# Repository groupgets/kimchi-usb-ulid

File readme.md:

# kimχ micro lid KiCad project template

This template lets you create lid expansion boards for the [kimχ micro i.MX8M Mini SBC](https://labs.groupgets.com/kimchi-micro).

This project should include everything you need to make an expansion board, including an eeprom
that can be used to identify your lid and automatically load the correct configuration files (with
some software work to support this).

## How to use this project

This project is to be used with KiCad's "New Project from Template" function.

### Download with GitHub

On GitHub you can select Clone or Download -> Download Zip, and save into your KiCad templates directory. The user template directory is $HOME/kicad/template/

In KiCad, select File > New Project > New Project From Template, and select User Templates. You can then select the kimχ micro - LID project in this list.

### Clone with GitHub

Alternatively, you can create a new GitHub project from this template by selecting Use This Template, above. From there you clone the new project locally and open it directly with KiCad.

Important Note
============
GroupGets does not provide coding, firmware, or software support of any kind and will not respond to related requests. All software and firmware provided by GroupGets are offered solely as examples or potential starting points. These repositories may be outdated and are not guaranteed to function as intended.

We do not accept returns or offer replacements due to issues related to software, firmware, or code compatibility.

The software is provided "AS IS", without warranty of any kind, express or implied, including but not limited to the warranties of merchantability, fitness for a particular purpose and non-infringement. In no event shall the authors or copyright holders be liable for any claim, damages, or other liability, whether in an action of contract, tort, or otherwise, arising from, out of, or in connection with the software or the use or other dealings in the software.

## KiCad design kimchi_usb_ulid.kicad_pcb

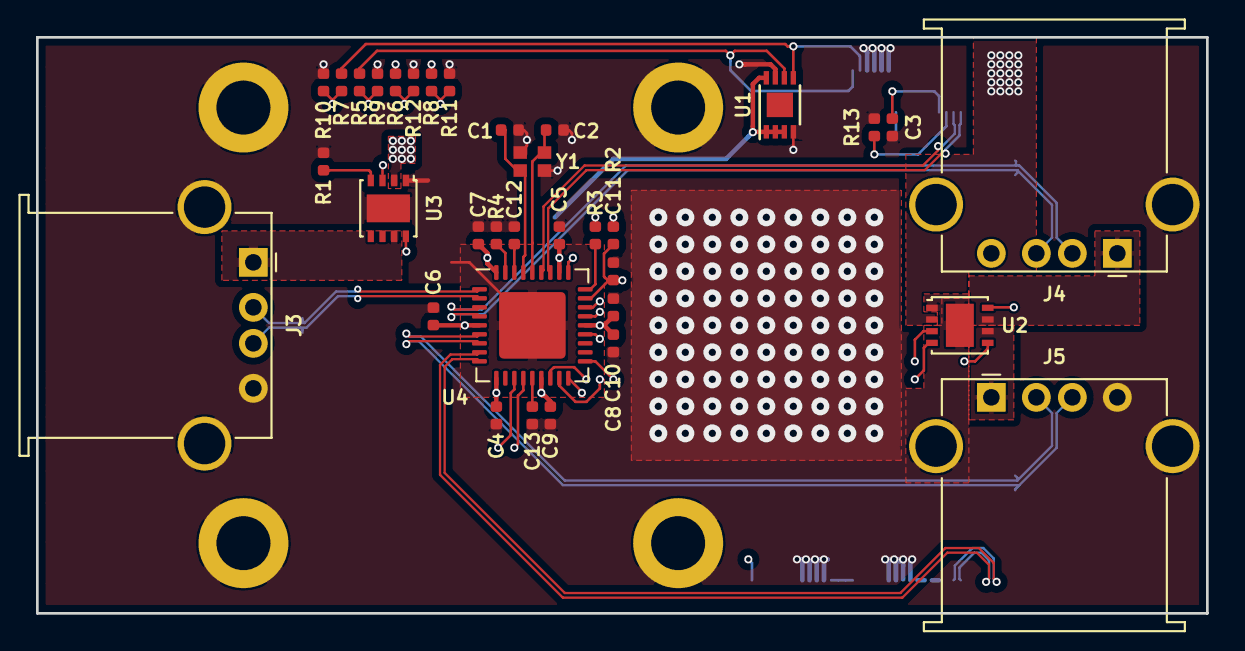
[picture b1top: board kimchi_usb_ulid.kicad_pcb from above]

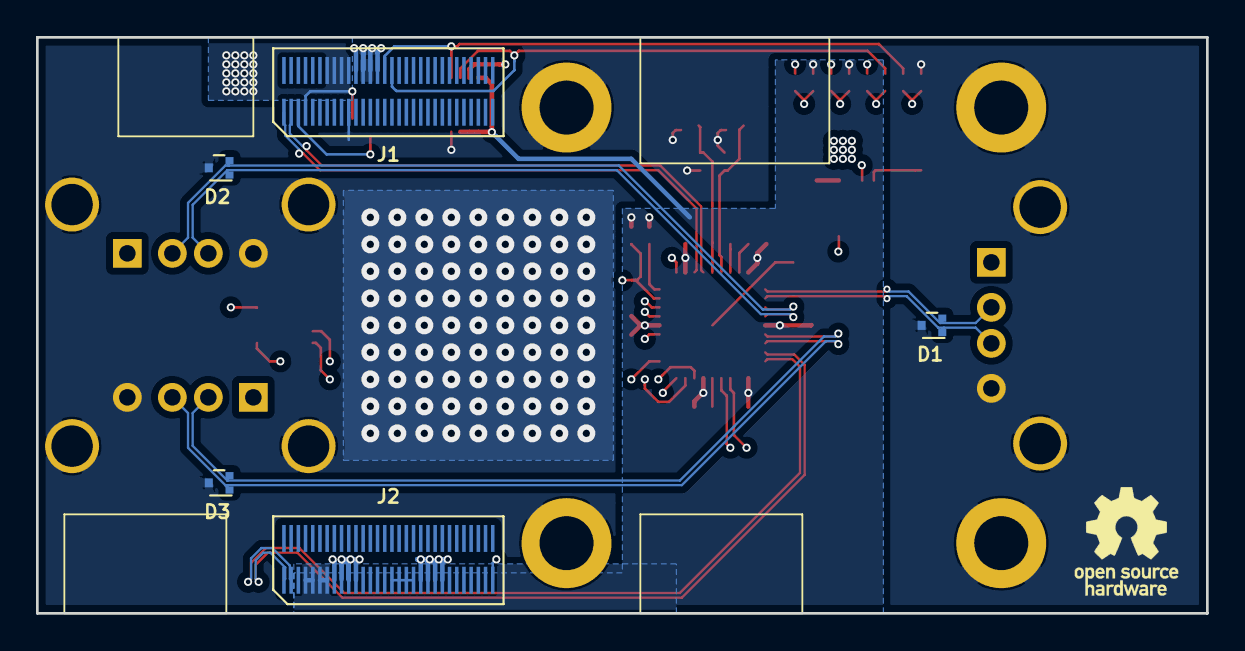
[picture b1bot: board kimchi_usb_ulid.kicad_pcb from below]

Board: 4 copper layers, 65.0 x 32.0 mm, 44 parts (6 on the bottom side), 38 nets.

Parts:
C1, C2: 18pF 1%; C_0402_1005Metric
C3: 1uF; C_0402_1005Metric
C4, C5, C6, C7, C8, C9, C11, C12, C13: 0.1uF; C_0402_1005Metric
C10: 4.7uF; C_0402_1005Metric
D1, D2, D3: D_TVS_x2_AAC; SOT-723
H1, H2, H3, H4: MountingHole_Pad; MountingHole_3mm_Pad
J1, J2: DF40HC(3.5)-60DS
J3, J4, J5: USB_A; USB_A_Stewart_SS-52100-001_Horizontal
LOGO1: Logo_Open_Hardware_Small; OSHW-Logo_5.7x6mm_SilkScreen
R1: 10K; R_0402_1005Metric
R2, R3, R6, R8, R9, R10, R11, R12, R13: 100K; R_0402_1005Metric
R4: 12K 1%; R_0402_1005Metric
R5, R7: 0; R_0402_1005Metric
U1: 24C32; DFN-8-1EP_3x2mm_P0.5mm_EP1.36x1.46mm
U2, U3: AP2152A; DFN-8-1EP_3x3mm_P0.65mm_EP1.55x2.4mm
U4: USB2514B_Bi; QFN-36-1EP_6x6mm_P0.5mm_EP3.7x3.7mm
Y1: 24MHz 50 PPM; XRCGB

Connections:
/USB_DN1_DN: D1.2, J3.2, U4.1
/USB_DN1_DP: D1.1, J3.3, U4.2
/USB_DN1_EN: U3.3, U4.12
/USB_DN1_FLG: U3.8, U4.13
/USB_DN1_VBUS: J3.1, U3.7
/USB_DN2_DN: D2.2, J4.2, U4.3
/USB_DN2_DP: D2.1, J4.3, U4.4
/USB_DN2_EN: U2.3, U4.16
/USB_DN2_FLG: U2.8, U4.17
/USB_DN2_VBUS: J4.1, U2.7
/USB_DN3_DN: D3.2, J5.2, U4.6
/USB_DN3_DP: D3.1, J5.3, U4.7
/USB_DN3_EN: U2.4, U4.18
/USB_DN3_FLG: U2.5, U4.19
/USB_DN3_VBUS: J5.1, U2.6
GND: C1.1, C2.1, C3.2, C4.1, C5.1, C6.1, C7.1, C8.1, C9.1, C10.1, C11.1, C12.1, C13.1, D1.3, D2.3, D3.3, H1.1, H2.1, H3.1, H4.1, J1.11, J1.12, J1.13, J1.14, J1.51, J2.38, J2.39, J2.40, J2.41, J2.50, J2.51, J2.52, J2.53, J3.4, J3.5, J4.4, J4.5, J5.4, J5.5, R1.2, R4.1, R9.2, R10.2, R11.2, R12.2, R13.1, U1.4, U1.7, U2.1, U2.9, U3.1, U3.9, U4.37, Y1.2, Y1.4
I2C4_SCL: J1.16, R5.2, U1.6
I2C4_SDA: J1.15, R7.1, U1.5
unnamed: C1.2, U4.33, Y1.3
unnamed: C2.2, U4.32, Y1.1
unnamed: C12.2, U4.34
unnamed: C13.2, U4.14
unnamed: R1.1, U3.4
unnamed: R3.1, U4.27
unnamed: R4.2, U4.35
unnamed: R5.1, R9.1, U4.24
unnamed: R7.2, R10.1, U4.22
unnamed: R8.1, R11.1, U4.28
unnamed: R6.1, R12.1, U4.25
PCIE_USB_D_N: J2.60, U4.8
PCIE_USB_D_P: J2.59, U4.9
SAI3_TXC: C11.2, J2.31, R2.1, U4.26
USB2_DN: J1.59, U4.31
USB2_DP: J1.60, U4.30
USB2_ID: J1.58, R13.2
USB2_VBUS: C3.1, J1.7, J1.8, J1.9, J1.10, J1.57, U2.2, U3.2
VDD_1V8: J2.42, J2.43, J2.44, J2.45
VDD_3V3: C4.2, C5.2, C6.2, C7.2, C8.2, C9.2, C10.2, J2.54, J2.55, J2.56, J2.57, R2.2, R3.2, R6.2, R8.2, U1.1, U1.2, U1.3, U1.8, U4.5, U4.10, U4.15, U4.23, U4.29, U4.36

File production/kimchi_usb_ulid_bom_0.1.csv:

Component,Description,Part,References,Value,Footprint,Quantity Per PCB,Vendorpart,Mfgrpart,Mfgr,Populate
1,Unpolarized capacitor,C,C4 C5 C6 C7 C8 C9 C11 C12 C13,0.1uF,C_0402_1005Metric,9,490-13341-1-ND,GRM155R71E104ME14D,Murata,
2,Unpolarized capacitor,C,C1 C2,18pF 1%,C_0402_1005Metric,2,490-16457-1-ND,GCM1555C1H180FA16D,Murata,
3,Unpolarized capacitor,C,C3,1uF,C_0402_1005Metric,1,490-12699-1-ND,GRM155C81A105KA12D,Murata,
4,Unpolarized capacitor,C,C10,4.7uF,C_0402_1005Metric,1,490-5408-1-ND,GRM155R60J475ME87D,Murata,
5,"Bidirectional dual transient-voltage-suppression diode, center on pin 3",D_TVS_x2_AAC,D1 D2 D3,D_TVS_x2_AAC,SOT-723,3,SZESD7205DT5GOSCT-ND,SZESD7205DT5G,ON,
6,"Generic connector, double row, 02x30, counter clockwise pin numbering scheme (similar to DIP packge numbering), script generated (kicad-library-utils/schlib/autogen/connector/)",Conn_02x30_Counter_Clockwise,J1 J2,DF40HC(3.5)-60DS,DF40HC(3.5)-60DS,2,H11917CT-ND,DF40HC(3.5)-60DS-0.4V(51),Hirose,
7,USB Type A connector,USB_A,J3 J4 J5,USB_A,USB_A_Stewart_SS-52100-001_Horizontal,3,380-1412-ND,SS-52100-001,Stewart,
8,Resistor,R,R2 R3 R13,100K,R_0402_1005Metric,3,311-100KLRCT-ND,RC0402FR-07100KL,Yageo,
9,Resistor,R,R1,10K,R_0402_1005Metric,1,311-10KJRCT-ND,RC0402JR-0710KL,Yageo,
10,Resistor,R,R4,12K 1%,R_0402_1005Metric,1,311-12.0KLRCT-ND,RC0402FR-0712KL,Yageo,
11,"I2C Serial EEPROM, 16Kb, DIP-8/SOIC-8/TSSOP-8/DFN-8",24LC16,U1,24C32,DFN-8-1EP_3x2mm_P0.5mm_EP1.36x1.46mm,1,497-15757-1-ND,M24C32-FMC6TG,ST,
12,Power Switch 1:2 P-Channel 500mA,AP2152A,U2 U3,AP2152A,DFN-8-1EP_3x3mm_P0.65mm_EP1.55x2.4mm,2,AP2152AFGEG-7DICT-ND,AP2152AFGEG-7,Diodes,
13,USB 2.0 Hi-Speed Hub Controller,USB2514B_Bi,U4,USB2514B_Bi,QFN-36-1EP_6x6mm_P0.5mm_EP3.7x3.7mm,1,USB2514B-AEZC-CT-ND,USB2514B-AEZC-TR,Microchip,
14,"Four pin crystal, GND on pins 2 and 4",Crystal_GND24,Y1,24MHz 50 PPM,XRCGB,1,490-5575-1-ND,XRCGB24M000F0L00R0,Murata,

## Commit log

2020-04-12 Created usb hub ulid
2020-04-12 Plot gerbers
2020-04-12 Change mask web to 3 mil
2020-04-19 Finish bom
